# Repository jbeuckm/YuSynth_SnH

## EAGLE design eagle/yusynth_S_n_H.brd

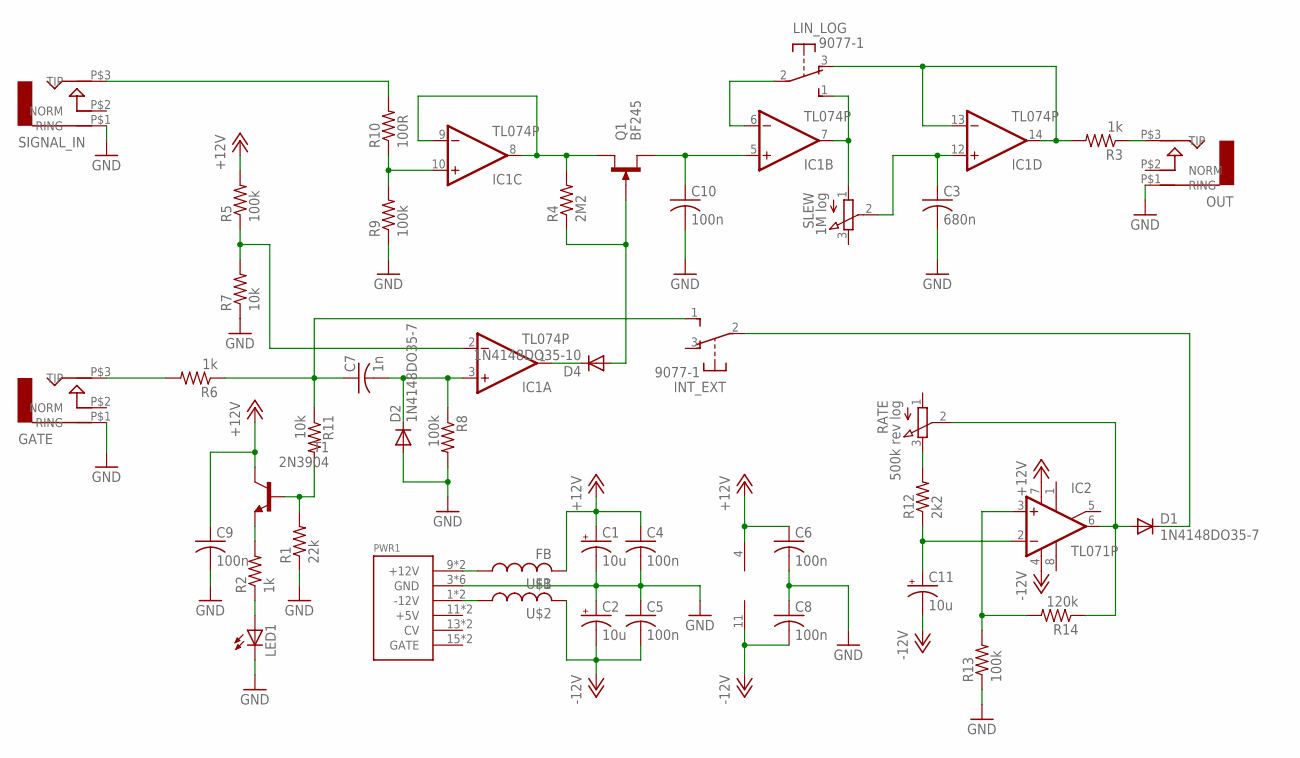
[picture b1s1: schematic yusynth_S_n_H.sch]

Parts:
C1, C2, C11: 10u; B45181A
C3: 680n; C050-024X044
C4, C5, C6, C8, C9, C10: 100n; C050-024X044
C7: 1n; C050-024X044
D1, D2: 1N4148DO35-7; DO35-7
D4: 1N4148DO35-10; DO35-10
GATE: AUDIO-JACK; ERTHENVAR-JACK-90DEG
IC1: TL074P; DIL14
IC2: TL071P; DIL08
INT_EXT: 9077-1
LED1: LED5MM
LIN_LOG: 9077-1
OUT: AUDIO-JACK; ERTHENVAR-JACK-90DEG
PWR1: POWER; POWER_16
Q1: BF245; SOT54C
R1: 22k; 0207/10
R2, R3, R6: 1k; 0207/10
R4: 2M2; 0207/10
R5, R8, R9, R13: 100k; 0207/10
R7, R11: 10k; 0207/10
R10: 100R; 0207/10
R12: 2k2; 0207/10
R14: 120k; 0207/10
RATE: 500k rev log; 3RP/1610N
SIGNAL_IN: AUDIO-JACK; ERTHENVAR-JACK-90DEG
SLEW: 1M log; 3RP/1610N
T1: 2N3904; TO92
U$1, U$2: FB

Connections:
+12V: C1.+, C4.1, C6.1, C9.1, IC1.4 (V+), IC2.7 (V+), R5.2, T1.1 (C), U$1.P$2 (2)
-12V: C2.-, C5.2, C8.2, C11.-, IC1.11 (V-), IC2.4 (V-), U$2.P$2 (2)
GND: C1.-, C2.+, C3.2, C4.2, C5.1, C6.2, C8.1, C9.2, C10.2, D2.A, GATE.P$1 (RING), LED1.K (C), OUT.P$1 (RING), PWR1.3 (GND), PWR1.4 (GND), PWR1.5 (GND), PWR1.6 (GND), PWR1.7 (GND), PWR1.8 (GND), R1.1, R7.1, R8.2, R9.1, R13.1, SIGNAL_IN.P$1 (RING)
unnamed: PWR1.9 (+12V), PWR1.10 (+12V), U$1.P$1 (1)
unnamed: PWR1.1 (-12V), PWR1.2 (-12V), U$2.P$1 (1)
unnamed: C7.1, INT_EXT.1 (S), R6.1, R11.1
unnamed: D4.C, IC1.1 (OUT)
unnamed: R2.2, T1.3 (E)
unnamed: D4.A, Q1.G, R4.1
unnamed: IC1.2 (-IN), R5.1, R7.2
unnamed: LED1.A, R2.1
unnamed: IC1.8 (OUT), IC1.9 (-IN), Q1.D, R4.2
unnamed: C7.2, D2.C, IC1.3 (+IN), R8.1
unnamed: IC1.13 (-IN), IC1.14 (OUT), LIN_LOG.3 (O), R3.2
unnamed: R12.2, RATE.3 (E)
unnamed: C3.1, IC1.12 (+IN), SLEW.2 (S)
unnamed: GATE.P$3 (TIP), R6.2
unnamed: OUT.P$3 (TIP), R3.1
unnamed: IC1.10 (+IN), R9.2, R10.1
unnamed: R10.2, SIGNAL_IN.P$3 (TIP)
unnamed: C10.1, IC1.5 (+IN), Q1.S
unnamed: IC1.7 (OUT), LIN_LOG.1 (S), SLEW.1 (A)
unnamed: IC1.6 (-IN), LIN_LOG.2
unnamed: R1.2, R11.2, T1.2 (B)
unnamed: IC2.3 (+IN), R13.2, R14.2
unnamed: C11.+, IC2.2 (-IN), R12.1
unnamed: D1.A, IC2.6 (OUT), R14.1, RATE.2 (S)
unnamed: D1.C, INT_EXT.2

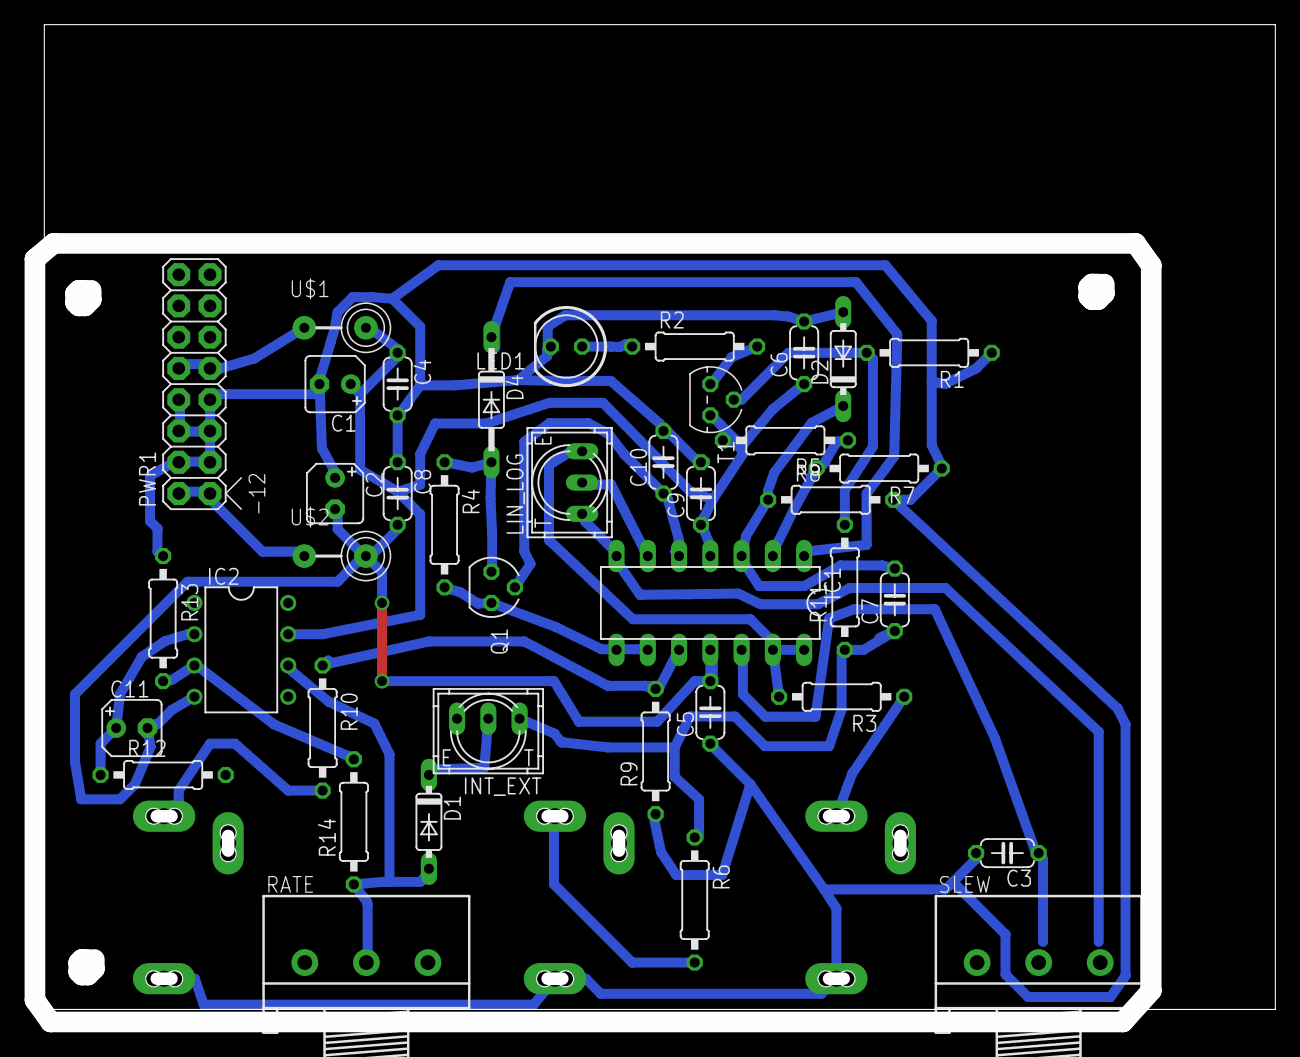
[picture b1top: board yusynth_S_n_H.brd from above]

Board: 2 copper layers, 100.8 x 81.0 mm, 43 parts (0 on the bottom side), 28 nets.

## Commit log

2016-01-11 schematic
2016-01-12 almost routed
2016-01-13 routed
2016-01-14 cutout
2016-01-14 gcode
2016-01-19 fixed an opamp output connection and spacing tweaks
2016-01-21 adjusted a spacing, removed ridiculous bus gate and corrected pot reversals
2016-01-21 routed to reflect last schemo changes
2016-01-21 gcode to reflect last schemo changes
